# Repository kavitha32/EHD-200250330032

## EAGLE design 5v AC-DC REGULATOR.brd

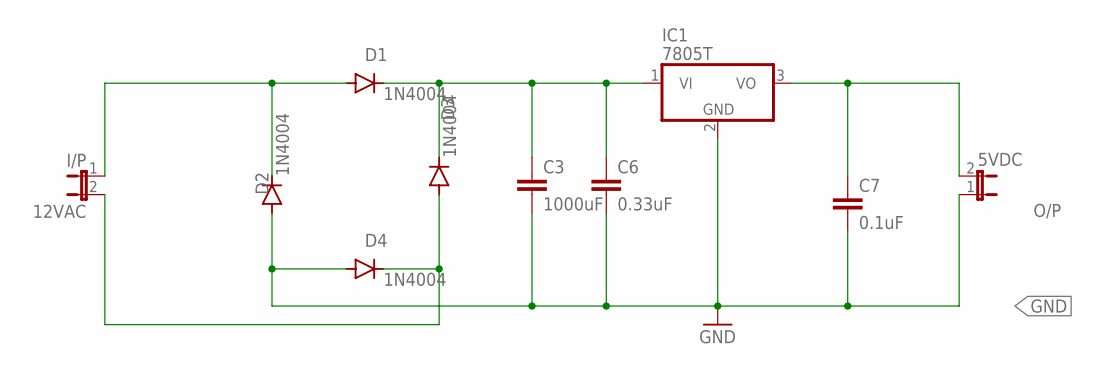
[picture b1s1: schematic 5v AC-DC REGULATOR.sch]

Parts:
C3: 1000uF; C2.5-3
C6: 0.33uF; C2.5-3
C7: 0.1uF; C2.5-3
D1, D2, D3, D4: 1N4004; DO41-10
I/P: 12VAC; JP1
IC1: 7805T; TO220H
O/P: 5VDC; JP1

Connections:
GND: C3.2, C6.2, C7.2, D2.A, D4.A, IC1.2 (GND), O/P.1
unnamed: C3.1, C6.1, D1.C, D3.C, IC1.1 (VI)
unnamed: D3.A, D4.C, I/P.2
unnamed: D1.A, D2.C, I/P.1
unnamed: C7.1, IC1.3 (VO), O/P.2

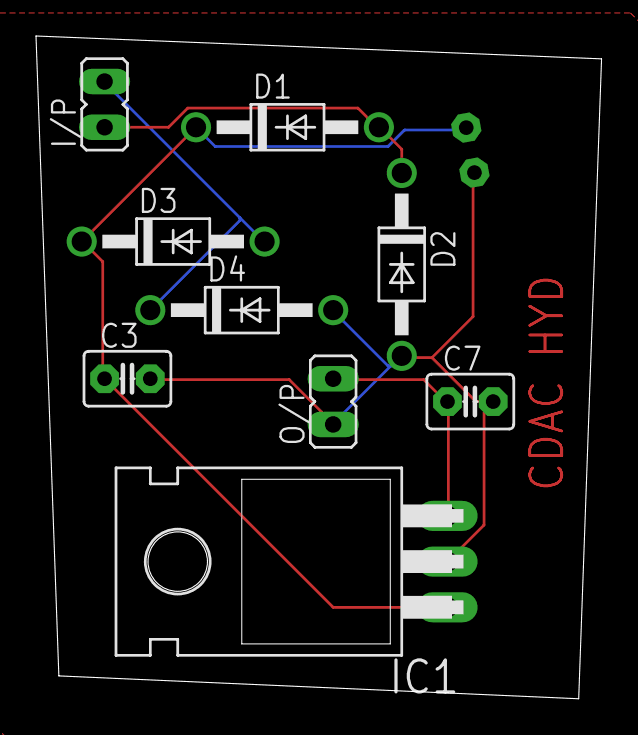
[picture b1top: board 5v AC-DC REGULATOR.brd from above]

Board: 2 copper layers, 31.4 x 36.8 mm, 10 parts (1 on the bottom side), 5 nets.
